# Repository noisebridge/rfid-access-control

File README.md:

RFID access control
-------------------

Access control system used within the [Noisebridge] hacker space.

   - RFID door terminal
      * [Firmware](software/firmware/README.md)
      * [PCB](hardware/terminal/README.md)
      * [3D printed case](hardware/terminal-case/README.md)
   - [Multi RS232 serial interface with RJ45](hardware/multi-interface/README.md)
   - [Earl: Central access control software](software/earl/README.md)

![RFID reader][case-image]

[case-image]: https://github.com/hzeller/rfid-access-control/raw/master/img/rfid-reader-case.png
[Noisebridge]: https://noisebridge.net/

## License

All code and PCB designs are released under the GNU General Public License V2, found in LICENSE

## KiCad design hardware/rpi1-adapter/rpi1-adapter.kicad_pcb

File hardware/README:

Case
   - a case to mount the RFID reader on the wall.

Boards
  - terminal board with RFID-RC522, providing a serial interface and potentially
    local switching
  - interface board on 'server' side, interfacing the Raspberry Pi or Beaglebone
    with the physical world of serial interfaces an relay switching.

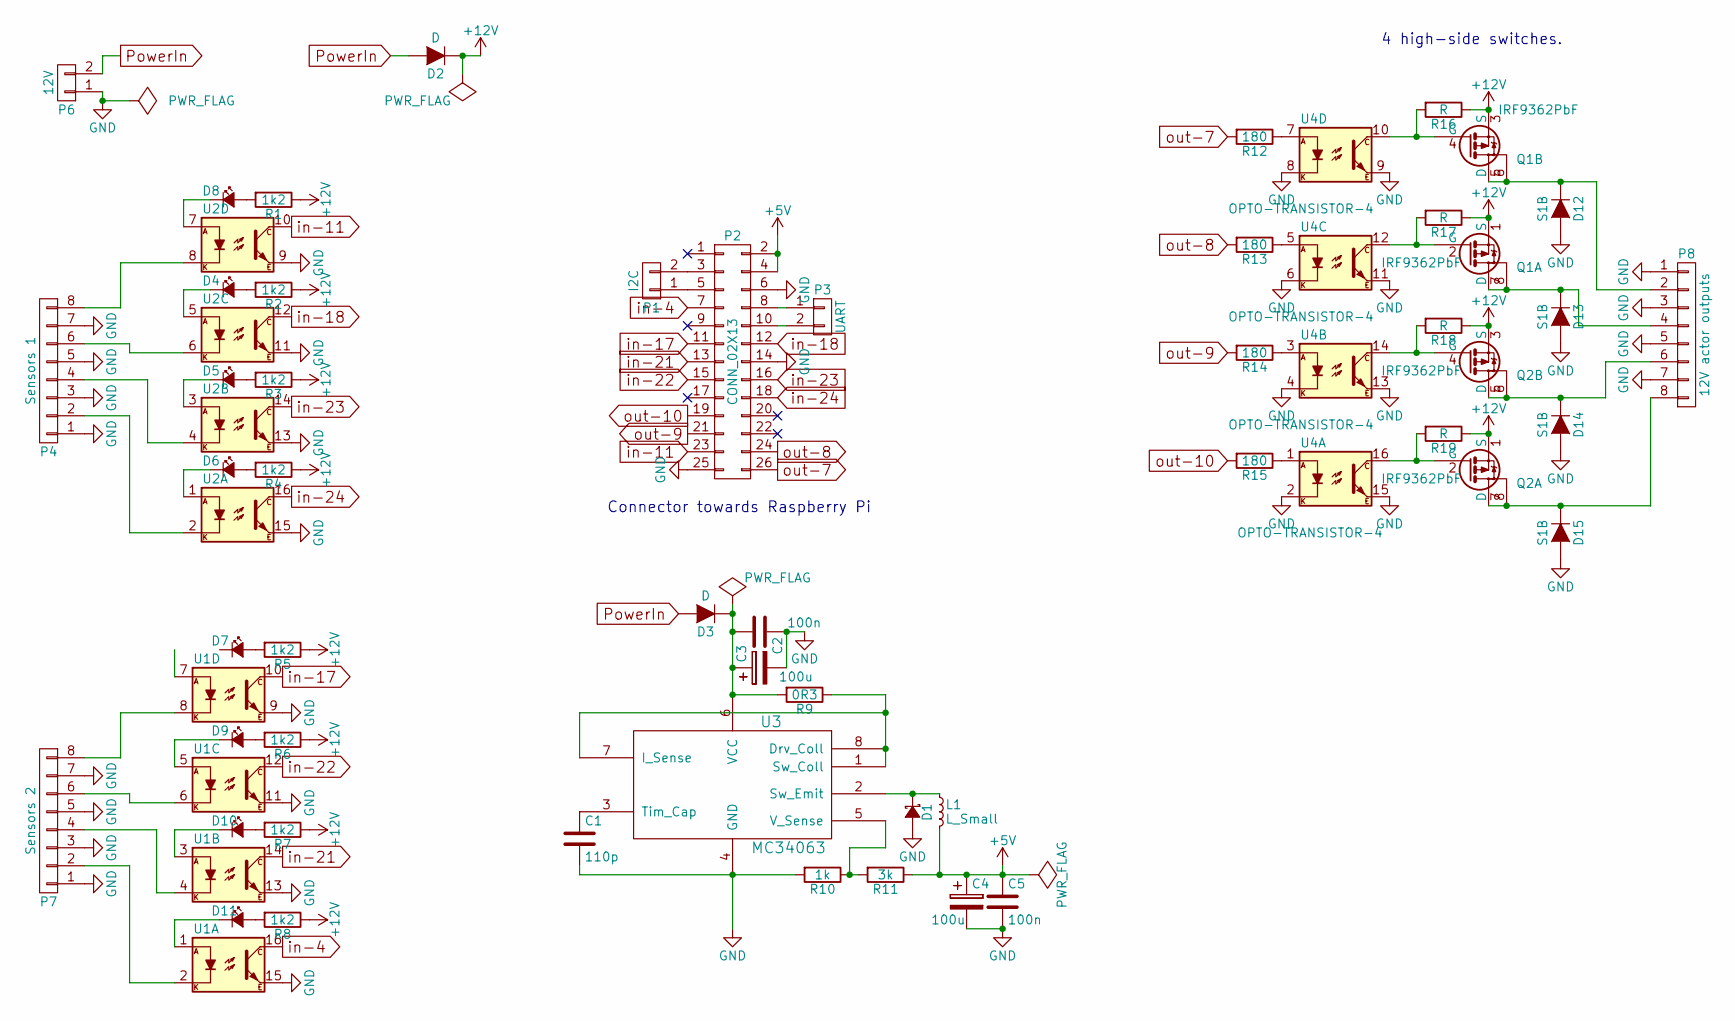
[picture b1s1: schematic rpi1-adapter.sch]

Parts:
C1: 110p; C_0805_HandSoldering
C2, C5: 100n; C_0805_HandSoldering
C3: 100u; C_Radial_D10_L16_P5
C4: 100u; C_1206_HandSoldering
D1: D_Schottky_Small; Diode-SMA_Handsoldering
D2, D3: D; Diode_DO-35_SOD27_Horizontal_RM10
D4, D5, D6, D7, D8, D9, D10, D11: Led_Small; LED-0805
D12, D13, D14, D15: S1B; Diode-SMA_Standard
L1: L_Small; INDUCTOR_V
P1: I2C; Pin_Header_Straight_1x02
P2: CONN_02X13; Pin_Header_Straight_2x13
P3: UART; Pin_Header_Straight_1x02
P4: Sensors 1; TerminalBlock-8pin-3.5mm
P6: 12V; JACK_ALIM
P7: Sensors 2; TerminalBlock-8pin-3.5mm
P8: 12V actor outputs; TerminalBlock-8pin-3.5mm
Q1, Q2: IRF9362PbF; SO-8
R1, R2, R3, R5, R6, R7, R8: 1k2; R_0805_HandSoldering
R4: 1k2; R_0805
R9: 0R3; R_0805_HandSoldering
R10: 1k; R_0805_HandSoldering
R11: 3k; R_0805_HandSoldering
R12, R13, R14, R15: 180; R_0805_HandSoldering
R16, R17, R18, R19: R; R_0805_HandSoldering
U1, U2, U4: OPTO-TRANSISTOR-4; DIP-16_W7.62mm_LongPads
U3: MC34063; SOIC-8_3.9x4.9mm_Pitch1.27mm

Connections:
+5V: C4.1, C5.1, L1.2, P2.2, P2.4, R11.1
+12V: D2.1 (K), Q1.1 (S), Q1.3 (S), Q2.1 (S), Q2.3 (S), R1.1, R2.1, R3.1, R4.1, R5.1, R6.1, R7.1, R8.1, R16.1, R17.1, R18.1, R19.1
GND: C1.2, C2.1, C3.2, C4.2, C5.2, D1.2 (A), D12.2 (A), D13.2 (A), D14.2 (A), D15.2 (A), P2.6, P2.14, P2.25, P4.1, P4.3, P4.5, P4.7, P6.1, P7.1, P7.3, P7.5, P7.7, P8.1, P8.3, P8.5, P8.7, R10.2, U1.9, U1.11, U1.13, U1.15, U2.9, U2.11, U2.13, U2.15, U3.4 (GND), U4.2, U4.4, U4.6, U4.8, U4.9, U4.11, U4.13, U4.15
unnamed: C1.1, U3.3 (Tim_Cap)
unnamed: C2.2, C3.1, D3.1 (K), R9.2, U3.6 (VCC)
unnamed: D1.1 (K), L1.1, U3.2 (Sw_Emit)
unnamed: D4.1 (K), U2.5
unnamed: D4.2 (A), R2.2
unnamed: D5.1 (K), U2.3
unnamed: D5.2 (A), R3.2
unnamed: D6.1 (K), U2.1
unnamed: D6.2 (A), R4.2
unnamed: D7.2 (A), R5.2
unnamed: D8.1 (K), U2.7
unnamed: D8.2 (A), R1.2
unnamed: D9.1 (K), U1.5
unnamed: D9.2 (A), R6.2
unnamed: D10.1 (K), U1.3
unnamed: D10.2 (A), R7.2
unnamed: D11.1 (K), U1.1
unnamed: D11.2 (A), R8.2
unnamed: D12.1 (K), P8.2, Q1.5 (D), Q1.6
unnamed: D13.1 (K), P8.4, Q1.7 (D), Q1.8
unnamed: D14.1 (K), P8.6, Q2.5 (D), Q2.6
unnamed: D15.1 (K), P8.8, Q2.7 (D), Q2.8
unnamed: P1.1, P2.5
unnamed: P1.2, P2.3
unnamed: P2.8, P3.1
unnamed: P2.10, P3.2
unnamed: P4.2, U2.2
unnamed: P4.4, U2.4
unnamed: P4.6, U2.6
unnamed: P4.8, U2.8
unnamed: P7.2, U1.2
unnamed: P7.4, U1.4
unnamed: P7.6, U1.6
unnamed: P7.8, U1.8
unnamed: Q1.2 (G), R17.2, U4.12
unnamed: Q1.4 (G), R16.2, U4.10
unnamed: Q2.2 (G), R19.2, U4.16
unnamed: Q2.4 (G), R18.2, U4.14
unnamed: R9.1, U3.1 (Sw_Coll), U3.7 (I_Sense), U3.8 (Drv_Coll)
unnamed: R10.1, R11.2, U3.5 (V_Sense)
unnamed: R12.1, U4.7
unnamed: R13.1, U4.5
unnamed: R14.1, U4.3
unnamed: R15.1, U4.1
PowerIn: D2.2 (A), D3.2 (A), P6.2
in-4: P2.7, U1.16
in-11: P2.23, U2.10
in-17: P2.11, U1.10
in-18: P2.12, U2.12
in-21: P2.13, U1.14
in-22: P2.15, U1.12
in-23: P2.16, U2.14
in-24: P2.18, U2.16
out-7: P2.26, R12.2
out-8: P2.24, R13.2
out-9: P2.21, R14.2
out-10: P2.19, R15.2

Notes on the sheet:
Connector towards Raspberry Pi
4 high-side switches.

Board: 2 copper layers, 53 parts (0 on the bottom side), 60 nets, no tracks yet.

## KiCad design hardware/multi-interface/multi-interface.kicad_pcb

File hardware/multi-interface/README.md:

Multi serial line driver RJ45
=============================

Features
--------
   - 4 interfaces with RJ45 plugs (uses a combined 4-block of RJ45 I found in
     an old switch. Standard distance would need to pull these apart 50 thou/mil)
   - TTL compatible with 3.3V, so can interface with Rasberry Pi or
     Beaglebone Black.
   - Creates RS232 line voltages from a single 3.3V supply.
   - Uses a [SP3232E][sp3232-spec], essentially a MAX232 compatible chip
     for 3.3V supply voltage and only 100nF capcitors needed.
   - Allows to power external terminals on Line 7 and 8 (see `../terminal` for
     details)
   - FYI M3 mounting holes are 18mmx64mm apart.

![PCB][pcb]

TODO
----
Learnings from first board, possibly add to second revision

   - It would be useful to have a four line voltage/ground connector, directly
      compatible with the corresponding 4-pin connector on the terminal side.
   - Silk-screen marking RX/TX
   - 3-Pin connector for 12v: [GND-12v-GND] to allow turn-agnostic plug.
   - Possibe protection circuit: reverse polarity protection diode; PTC fuse
   - optional 12V power LED ? Maybe optional 3.3V power LED
   - RX/TX LEDs. Check connection of RJ45 plugs, some have built-in LEDs
     (usually to indicate Ethernet 100Mbps/1Gbps), would be cool to re-use
     these. Also optional space for discrete diodes.
   - All LEDs: also provide pads on the bottom of the board if that is the
     part visible.
    
[pcb]: https://github.com/hzeller/rfid-access-control/raw/master/img/multi-interface-pcb.png
[sp3232-spec]: http://www.exar.com/common/content/document.ashx?id=619

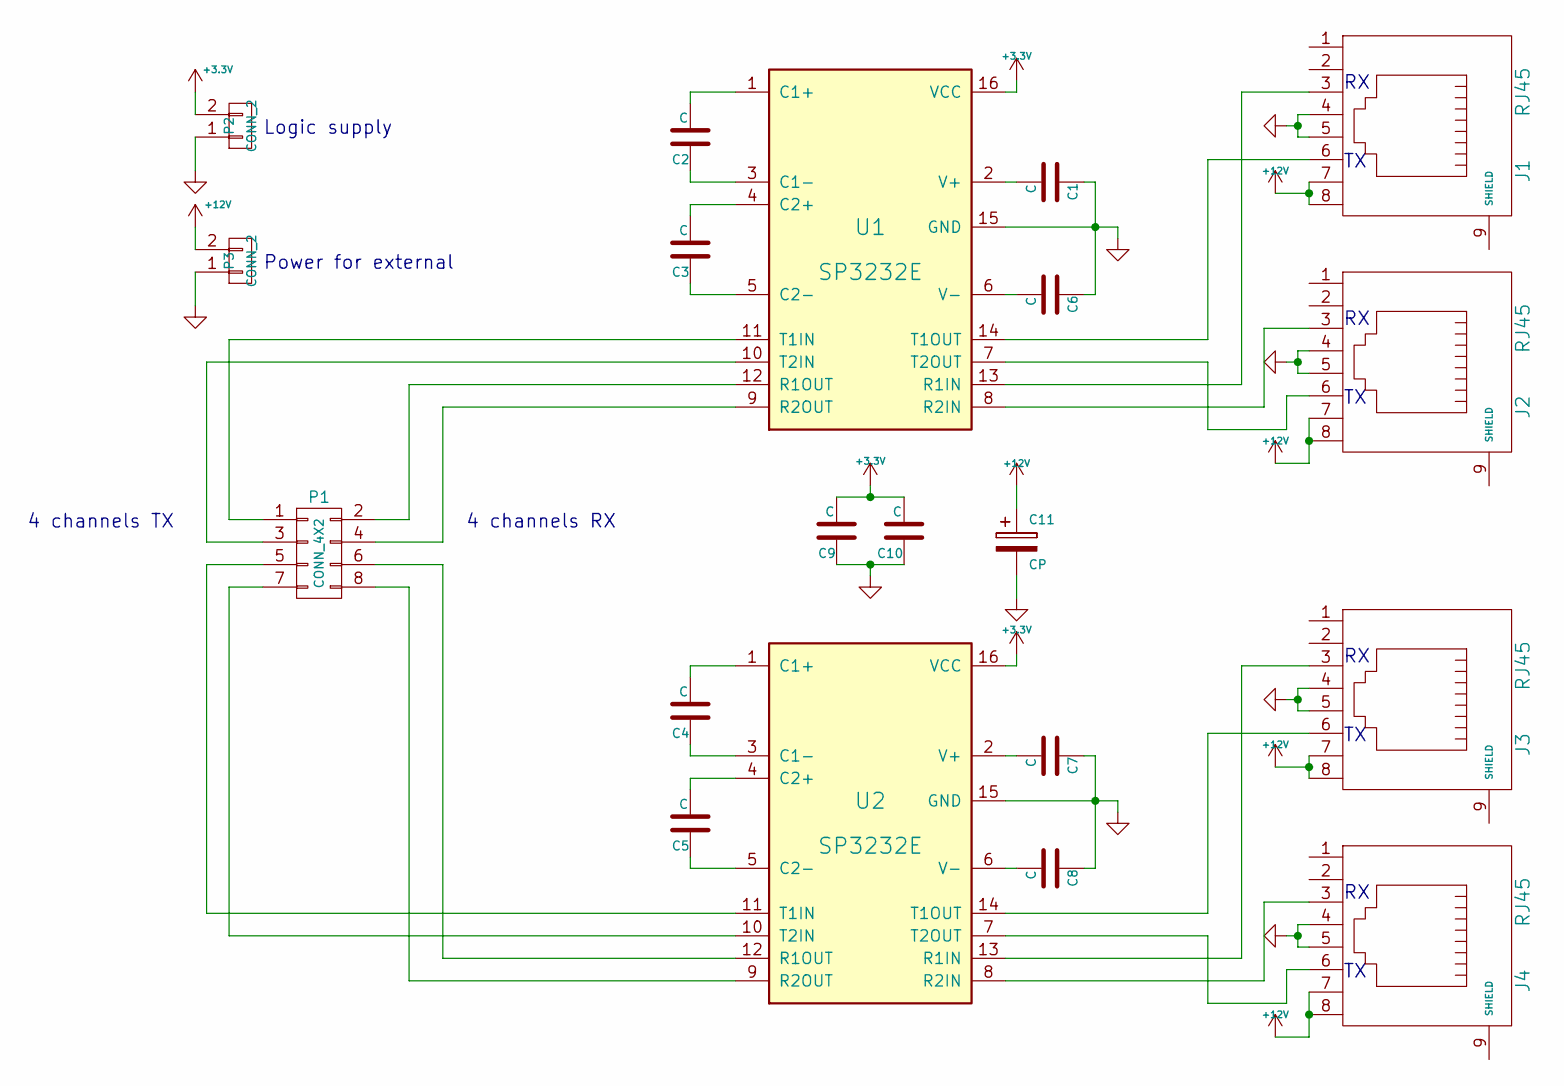
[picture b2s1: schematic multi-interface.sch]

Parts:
C1, C2, C3, C4, C5, C6, C7, C8, C9, C10: C; SMD-0805
C11: CP; Elko_vert_DM6-3_RM2-5
J1, J2, J3, J4: RJ45; RJ45_8
P1: CONN_4X2; Pin_Header_Straight_2x04
P2, P3: CONN_2; SIL-2
U1, U2: SP3232E; TSSOP-16

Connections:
+3V3: C9.2, C10.2, P2.2, U1.16 (VCC), U2.16 (VCC)
+12V: C11.1, J1.7, J1.8, J2.7, J2.8, J3.7, J3.8, J4.7, J4.8, P3.2
GND: C1.1, C6.1, C7.1, C8.1, C9.1, C10.1, C11.2, J1.4, J1.5, J2.4, J2.5, J3.4, J3.5, J4.4, J4.5, P2.1, P3.1, U1.15 (GND), U2.15 (GND)
unnamed: C1.2, U1.2 (V+)
unnamed: C2.1, U1.3 (C1-)
unnamed: C2.2, U1.1 (C1+)
unnamed: C3.1, U1.5 (C2-)
unnamed: C3.2, U1.4 (C2+)
unnamed: C4.1, U2.3 (C1-)
unnamed: C4.2, U2.1 (C1+)
unnamed: C5.1, U2.5 (C2-)
unnamed: C5.2, U2.4 (C2+)
unnamed: C6.2, U1.6 (V-)
unnamed: C7.2, U2.2 (V+)
unnamed: C8.2, U2.6 (V-)
unnamed: J1.3, U1.13 (R1IN)
unnamed: J1.6, U1.14 (T1OUT)
unnamed: J2.3, U1.8 (R2IN)
unnamed: J2.6, U1.7 (T2OUT)
unnamed: J3.3, U2.13 (R1IN)
unnamed: J3.6, U2.14 (T1OUT)
unnamed: J4.3, U2.8 (R2IN)
unnamed: J4.6, U2.7 (T2OUT)
unnamed: P1.1, U1.11 (T1IN)
unnamed: P1.2, U1.12 (R1OUT)
unnamed: P1.3, U1.10 (T2IN)
unnamed: P1.4, U1.9 (R2OUT)
unnamed: P1.5, U2.11 (T1IN)
unnamed: P1.6, U2.12 (R1OUT)
unnamed: P1.7, U2.10 (T2IN)
unnamed: P1.8, U2.9 (R2OUT)

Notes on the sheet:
4 channels RX
4 channels TX
Logic supply
Power for external

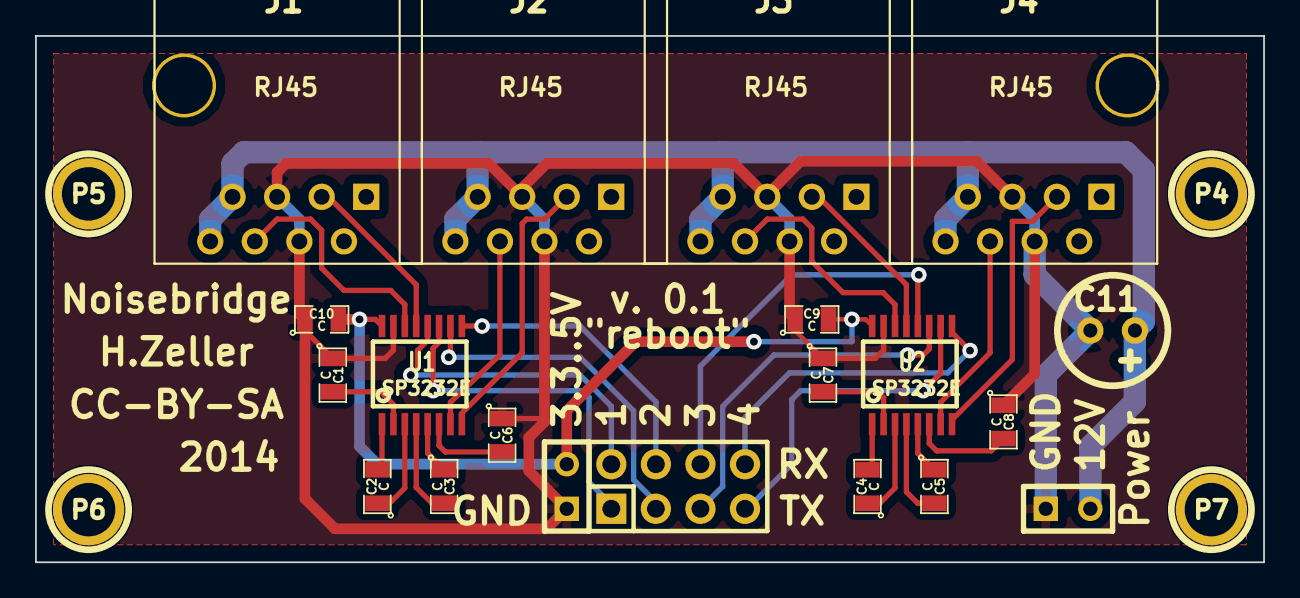
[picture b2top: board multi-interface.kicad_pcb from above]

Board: 2 copper layers, 70.0 x 30.0 mm, 24 parts (0 on the bottom side), 31 nets.

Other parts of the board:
P4, P5, P6, P7: CONN_1; 1pin

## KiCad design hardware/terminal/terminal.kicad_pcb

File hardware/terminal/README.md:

Terminal PCB
============

The Access terminal mounted at the outside of the door. Typically connecting the
RFID reader (via SPI interface), but also a 4x3 keypad (or just simple door-bell
button) and an LCD can be connected. If wanted, even an electric strike via
some external H-bridge.

This is based on an Atmega8 because I had a bunch lying around, but the DIL
version is bulky and ideally, I'd like to have a bit more IO pins, such as
for a 4th row of the keypad or separate LED outputs; future versions might
change to atmega168 (currently the best Atmel-IO bang for the buck).

This board provides the necessary breakouts to connect the peripherals to an
Atmega8 and holds the MAX232 compatible line driver.
The software in `../../software/firmware` makes it useful.

For a housing of this board and the RFID reader, have a look at
`../terminal-case`

Feature overview
----------------

   - Sized so that it can be sandwiched with a RFID-RC522 board (40mmx60mm),
     including the same mounting holes.
   - Communication via RS232, using standard RJ45 plug.
   - Separate 4-pin header to connect without RJ45
   - In-circuit programming header.
   - Uses Atmega8 in PDIP cases, mostly because I had a bunch lying around :)
   - Allows to connect RFID-RC522, 4x3 keypad, HD44780 LCD, RGB-LED,
     speaker-buzzer. All supported by firmware.
   - Uses a [SP3232E][sp3232-spec], essentially a MAX232 compatible chip
     for 3.3V supply voltage and only 100nF capcitors needed.
   - Uses the SP3232E charge pump to get the negative voltage needed to drive
     LCD contrast.
   - Little 'breadboard area' for quick hacks.

Serial connection with RJ45
---------------------------

Pinout of RJ45 is a somewhat 'standard' way to connect an RJ45 with RS232
and is used in [Various][rj45-terminal-1] [router][rj45-terminal-2]
terminal connections (But note to whoever came up with this first probably 20
years ago: **bad choice**! Pin 3 and 6 are twisted together in an ethernet
cable, so this just optimized crosstalk between RX and TX...).

We also power the terminal circuit via the RJ45. We use the fact that the
lines `DTR` and `RTS` can always be set to +12V safely (within RS232 voltage
range) from the host (=[Data Terminal Equipment; DTE][DTE]). We use that to
provide power to our terminal (for any other endpoint with RJ45, this set-up
would look like a benign 'always ready' flow control signal; so does not damage
equipment). With two lines providing power, it should be possible to power
smallish loads such as an electric strike even over a longer line without too
much voltage drop.

The following list is the RJ45 connections from view of the terminal,
the [DCE side][DCE].
The *Line* in the following list represents the corresponding RJ45 pin.
Also as reference gives the [9-pin Sub-D connector (DB9)][db9-pinout]
equivalent connection on a 'standard' connector.
NB: Depending on the wiring (T568A or T568B), the color of Line-3 is either
striped orange or green, the Line-6 solid orange or green.

   - Line 1: Not connected (usually: DCE:RTS (out) / DTE:CTS (in)) *DB9-8*
   - Line 2: Not connected (usually: DCE:DTR (out) / DTE:DSR (in)) *DB9-1*
   - Line 3: **TxD**  (on host DTE:RxD) *DB9-2* (orange or green striped)
   - Line 4: **GND** (on host DTE:RI, 'Ring indicator') *DB9-5* (DB9-9). (Blue solid).
   - Line 5: **GND** (GND) *DB9-5* (Blue striped).
   - Line 6: **RxD** (on host DTE:TxD) *DB9-3*  (orange or green solid)
   - Line 7: **12V** supply in (usually: DCE:DSR (in) / DTE:DTR (out), DB9-4; but not connected there, just constantly powered. (Brown striped).
   - Line 8: **12V** supply in (usually: DCE:CTS (in) / DTE:RTS (out), DB9-7; powered, dito) (Brown solid).

(Let's see how well RS232 works, if long lines create trouble, we might consider
RS422 physical).

Hacking DB9 to RJ45 connector
------------------------------
If you want to have a standard DB9-female to RJ45 connector work with
this terminal, you need to hack it: open it up, and *disconnect* the cables
that go to **DB4** and **DB7** and instead connect them to an external 12V
power supply, with ground connected to **DB5** (ideally, you'd provide some
current limiting like 500mA to the 12V line; so if things go wrong, not
catastrophically so).

Double check on the RJ45 connector, that line 4 and 5 are on ground,
Line 7 and 8 on +12V.

![PCB][pcb]

Assembly
--------
Watch out in this version of the board, the [LD1117] LDO has to be soldered
in differently than the board suggests.

Unfortunately, it has a different pintout than other voltage regulators, this
is why it slipped in. Instead of [`Vin`, `GND`, `Vout`], it is
[`GND`, `Vout`, `Vin`]. So you need to solder in some lead-twisting :)

Tip for the RC522 reader. Depending on how you sandwich it, the chrystal oscillator it
has on top pokes out to the front; it might make sense to resolder it and put on the back
of the board.

TODO
----
TODOs for future versions; learning from previous board

   - Switch to atmega168 with less bulky 32 TQFP and 4 more IO pins.
   - Fix pin-out of LDO (also, switch to ceramic capacitors for less
     board height)
   - In general optimize board for best stacking, e.g. avoid collision with
     the crystal on the RFID board.
   - Provide an extra fourth column for keypad.
   - separate connector for 4st row, 4th column for an optional door-bell.
   - Silkscreen label all the pins for RC522 to minimize confusion which way
     to stack.
   - separate out RGB LEDs from LCD (when more IO available)
   - Maybe provide a reverse 8x2 connector for LCD (some LCDs are better
     connected from the reverse side)
   - Provide additional 16x1 connector to simply connect these LCD types.
   - Directly mount RGB LED on bord for less mouting hassle
   - Separate RX/TX connector on TTL side for easier testing.
   - Add space for 754410 to possibly directly drive door-strikes.
   - Add space for extra transistor to amplify speaker output.
   - Add space for little buzzer on-board.
   - Input for a reed switch to detect open doors ?

![Schematic][schematic]

[pcb]: ../../img/terminal-pcb.png
[schematic]: ../../img/terminal-sch.png
[sp3232-spec]: http://www.exar.com/common/content/document.ashx?id=619
[rj45-terminal-1]: http://www.allpinouts.org/index.php/Cisco_Console_RJ45_to_DB9_Pin
[rj45-terminal-2]: http://kb.juniper.net/InfoCenter/index?page=content&id=KB13272
[db9-pinout]: http://www.db9-pinout.com/
[DTE]: http://en.wikipedia.org/wiki/Data_terminal_equipment
[DCE]: http://en.wikipedia.org/wiki/Data_circuit-terminating_equipment
[LD1117]: http://www.st.com/web/en/resource/technical/document/datasheet/CD00000544.pdf

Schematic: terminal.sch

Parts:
C1, C2, C3, C4, C5, C6, C9: C; c_0805
C7, C8: CP; Elko_vert_DM5_RM2-5
IC1: ATMEGA8-P; DIP-28__300
J1: RJ45; RJ45_8
P1: Prog; SIL-5
P2: RC522; SIL-8
P3: LCD; Pin_Header_Straight_2x08
P4: Keypad; Pin_Header_Straight_2x08
P5, P6, P7, P8: CONN_1; 1pin
P9: CONN_2X2; Pin_Header_Straight_2x02
P10, P12: CONN_4; SIL-4
P11, P14: CONN_5X2; Pin_Header_Straight_2x05
P13: CONN_3X2; Pin_Header_Straight_2x03
R1, R5: 2.2k; SMD-0805
R2: 2.2k; SM0805
R3, R4: 82; SM0805
R6: 3k; SMD-0805
R7: 12; SMD-0805
U2: SP3232E; TSSOP-16
U3: 7803; LM78XXV

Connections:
+3V3: C5.1, C6.1, C8.1, C9.1, IC1.7 (VCC), P2.8, P3.2, R1.1, R2.1, R7.1, U2.10 (T2IN), U2.16 (VCC), U3.VO
+12V: C7.1, J1.7, J1.8, P10.4, U3.VI
/CS-RFID: IC1.16 ((~SS~/OC1B)PB2), P2.1, R1.2
/RST-RFID: IC1.15 ((OC1A)PB1), P2.7
GND: C3.1, C4.1, C5.2, C6.2, C7.2, C8.2, C9.2, IC1.8 (GND), J1.4, J1.5, J1.9 (SHIELD), P1.1, P2.6, P3.1, P3.5, P3.16, P4.2, P4.4, P4.6, P4.8, P4.10, P4.12, P4.14, P4.16, P9.1, P9.3, P10.1, R5.2, U2.8 (R2IN), U2.15 (GND), U3.GND
KCOL-0: IC1.14 ((ICP)PB0), P4.7
KCOL-1: IC1.9 (PB6(XTAL1/TOSC1)), P4.5
KCOL-2: IC1.10 (PB7(XTAL2/TOSC2)), P4.3
KROW-0: IC1.6 ((XCK/T0)PD4), P4.15
KROW-1: IC1.11 ((T1)PD5), P4.13
KROW-2: IC1.12 ((AIN0)PD6), P4.11
KROW-3: IC1.13 ((AIN1)PD7), P4.9
LCD-D0: IC1.23 ((ADC0)PC0), P3.11
LCD-D1: IC1.24 ((ADC1)PC1), P3.12
LCD-D2: IC1.25 ((ADC2)PC2), P3.13
LCD-D3: IC1.26 ((ADC3)PC3), P3.14
LCD-EN: IC1.28 ((ADC5/SCL)PC5), P3.6
LCD-RS: IC1.27 ((ADC4/SDA)PC4), P3.4
LCD-contr: R6.2, U2.7 (T2OUT)
MISO: IC1.18 ((MISO)PB4), P1.3, P2.4
MOSI: IC1.17 ((MOSI/OC2)PB3), P1.4, P2.3
unnamed: C1.1, U2.1 (C1+)
unnamed: C1.2, U2.3 (C1-)
unnamed: C2.1, U2.4 (C2+)
unnamed: C2.2, U2.5 (C2-)
unnamed: C3.2, U2.2 (V+)
unnamed: C4.2, U2.6 (V-)
unnamed: IC1.1 (PC6(~RESET~)), P1.5, R2.2
unnamed: IC1.4 ((INT0)PD2), R3.2
unnamed: IC1.5 ((INT1)PD3), R4.2
unnamed: P3.3, R5.1, R6.1
unnamed: P3.15, R7.2
unnamed: P9.2, R3.1
unnamed: P9.4, R4.1
RX: IC1.2 ((RXD)PD0), U2.12 (R1OUT)
RX-ext: J1.6, P10.3, U2.13 (R1IN)
SCK: IC1.19 ((SCK)PB5), P1.2, P2.2
TX: IC1.3 ((TXD)PD1), U2.11 (T1IN)
TX-ext: J1.3, P10.2, U2.14 (T1OUT)

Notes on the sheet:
Playground Area
Background Light

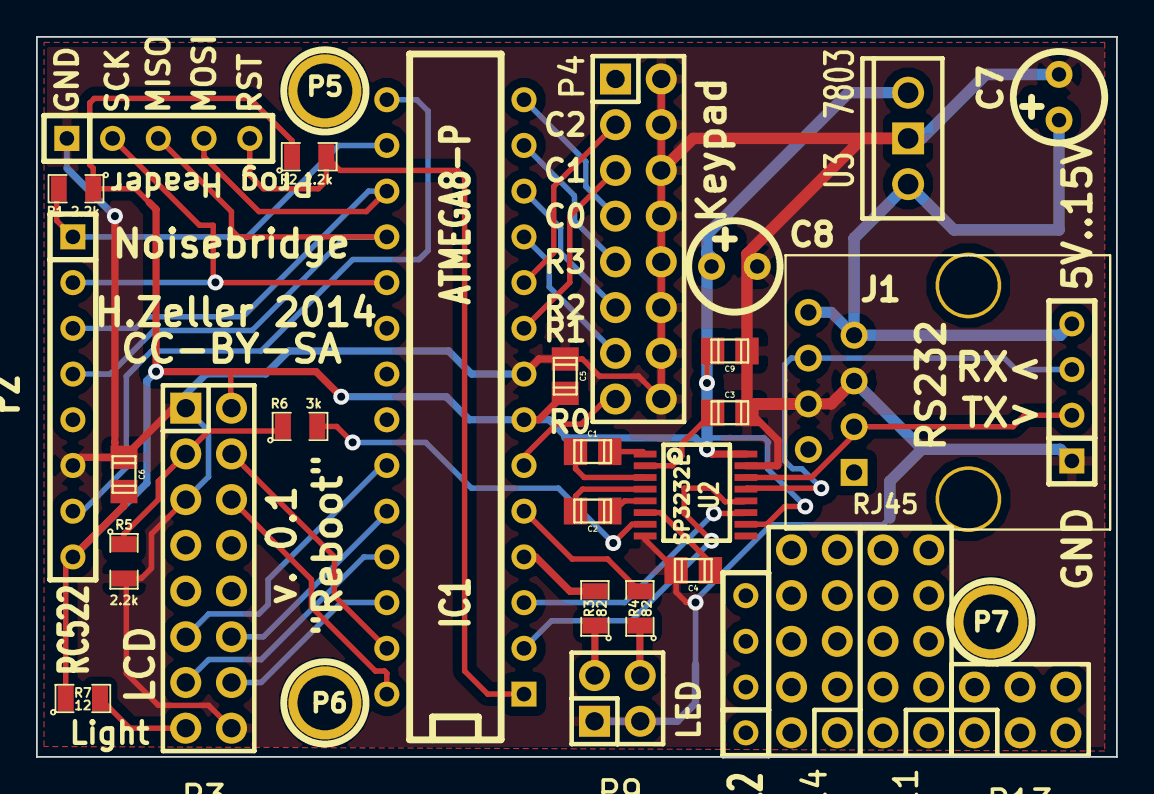
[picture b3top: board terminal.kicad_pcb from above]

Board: 2 copper layers, 60.0 x 40.0 mm, 33 parts (0 on the bottom side), 39 nets.

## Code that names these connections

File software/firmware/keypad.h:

/* -*- mode: c++; c-basic-offset: 2; indent-tabs-mode: nil; -*-
 * Copyright (c) h.zeller@acm.org. GNU public License.
 */

#ifndef AVR_KEYPAD_H_
#define AVR_KEYPAD_H_

#include "clock.h"

// For wiring more like 'pretty' physical layout, logical layout is a mess
// with bits distributed between ports :)
// row 1:PD7 2:PD6 3:PD5 4:PD4  (all port D; conveniently shifted by 4)
// col 1:PB0 2:PB7 3:PB6        (all port B)
class KeyPad {
  enum {
    // We read from Port-D to top 4 bits
    ROW_PORTD_SHIFT = 4,

    // Columns will be outputs on Port-B
    COL_1 = (1<<0),
    COL_2 = (1<<6),
    COL_3 = (1<<7),
    PORTB_OUT_MASK = COL_1 | COL_2 | COL_3,
  };

public:
  KeyPad();

  // This method needs to be called regularly.
  // It returns the current character pressed on the keypad if it settled
  // for long enough (it returns it only once, no auto-repeat).
  // Returns a NUL character ('\0') if no key is pressed.
  char ReadKeypad();

private:
  typedef unsigned char keypad_state_t;
  keypad_state_t SampleCol(unsigned char col_sample_bit,
                           keypad_state_t col_data);
  keypad_state_t readKeypadState();

  keypad_state_t current_state_;
  bool character_returned_;
  Clock::cycle_t start_time_;
};

#endif  // AVR_KEYPAD_H_

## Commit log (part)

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2014-08-28 o Move third party mfrc library in separate directory
2014-08-28 o rename ALLOW_BAUD_CHANGE -> FEATURE_BAUD_CHANGE
2014-09-01 o Some pseudo-code. To be removed, code should be go
2014-09-03 o sandwich turned out a bit thicker.
2014-09-03 o Update README with specs.
2014-09-03 o qualify Baron with a link.
2014-09-03 o Update readme.
2014-09-03 o Rename host -> earl. As this is our go package name.
2014-09-03 o fix typo.
2014-09-03 Initial submit of earl server with a debug handler.
2014-09-03 o Update build doc.
2014-09-03 o add GetTerminalName()
2014-09-03 o add comment regarding implementation of timeout.
2014-09-03 o more fmt -> log conversions.
2014-09-14 First draft of SSH server
2014-09-26 More authenticator work
2014-10-20 o Make keypress timeout dependent on time not ticks
2014-10-23 o Add assembly caveat.
2014-10-25 o Provide a flag toggle command to set operational flags. o Use that to switch on/off keypad tone feedback.
2014-10-25 Clean up code handling a bit
2014-10-26 It works!
2014-10-26 o Make TerminalStub an interface. That way, we can write unittests.
2014-10-26 o Little comment updates. o Do tick every 500ms
2014-10-27 o Do name dispatching.
2014-10-27 Use time.Duration for durations.
2014-10-27 o Move actions (operate relays) into GPIOActions and make DoorActions an interface.
2014-10-27 o A bit nicer timeout handling.
2014-10-27 Test for AccessHandler.
2014-10-28 o Add AddNewUser() in authenticator o Basic test for authenticator
2014-10-28 o Refine test a bit
2014-10-28 o Make user files configurable with flags.
2014-10-28 o Simplify switch/case that only contains one case with if
2014-10-28 o Be more in the spirit of Go and use ugly constant names (Did the commit message sound judging in any way ?)
2014-10-29 o stub for a time-test.
2014-10-29 o Move user-level to the front.
2014-10-29 o Just learned about the comma-separation of cases in switch.
2014-10-29 o Log if a door is opened.
2014-10-29 o Install: use install instead of cp, otherwise 'busy textfile' o time: make 22 inclusive
2014-10-29 o Remove a former todo.
2014-10-30 o We still want to find users with too short code; just not authenticate.
2014-10-30 o Update comments.
2014-10-31 o Add concept of expiry of codes without a contact info. Without contact info, it is not possible to find the 'right' line to remove in CSV in case the token is lost or stolen - people usually don't 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
2014-10-31 o Accidentally created validUsers map twice.
2014-10-31 o Instead of just logging error conditions, bubble them up using Go's tuple return. That way, they can be used/presented where needed.
2014-10-31 o Simple base-plates to mount inside box.
2014-11-02 o Add baseplate design files.
2014-11-03 o Logging: add starting info.
2014-11-03 o fix typo
2014-11-03 o A bit more logging how many codes were read.
2014-11-03 o Rename Handler to TerminalEventHandler : better reflects what it is doing.
2014-11-05 o Both plates are the same width, so make the holder for it a bit wider. Let's see if the overhang is managed properly by the printer.
2014-11-05 o Remove legacy file support. If we want to add PIN code access we still can do that with the new file format, no need to keep the old one.
2014-11-05 o DoorAction: Make logging more consistent for grepping.
2014-11-05 o More detailed stats while loading file.
2014-11-05 o Reasons for non-auth: handle most specific first.
2014-11-07 o initial version control terminal
2014-11-08 o Test validity of Level while reading.
2014-11-10 o make side-holder with step.
2014-11-10 o Remove feature to directly write to outputs. Was needed in debugging but not anymore.
2014-11-12 o if the manual drilled holes don't fit the print, make the print fit the holes ...
2014-11-12 o A bit more qualified messages on UI display.
2014-11-13 o Add an compile-optional feature to query the MFRC522 registers for debugging purposes.
2014-11-14 o remove obsolete comment.
2014-11-30 o Power colors.
2015-01-20 o Simplify earl startup.
2015-01-20 o ... make compile
2015-01-21 o Start a more random number for user-id generation.
2015-01-21 o Old compilers can't see unreachable code.
2015-01-22 o Make it possible to compile-in terminal name. o directly read from EEPROM when querying name; no need to copy it to RAM first.
2015-01-25 o Remove yeoman for now.
2015-01-25 o Move case/ -> terminal-case/
2015-01-26 o initial stub for UpdateUser() (TODO: persist)
2015-01-26 o readme.
2015-01-27 o progress database
2015-01-28 o Enable brown-out fuse (yeah, was disabled all the time :/) o Skip first byte in EEPROM, as this seems to be most vulnerable in power-glitch situations.
2015-01-28 o Provide update user.
2015-01-28 o Simple update user.
2015-01-28 o Rename TerminalStub to TerminalImpl o Re-arrange some methods for readability (public methods first, then private) in TerminalImpl. o make all private methods lower-case o IdleTick: It can starve, 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
2015-01-28 o Add doorbell action - if user out of daytime attempts to open door (and gets 'blue' result), it automatically triggers the doorbell. - Pressing a single '#' on the keypad without any number trigger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
2015-01-29 o Don't explicitly log door open events (SD card wear!)
2015-01-30 o Make it possible to query the access hours.
2015-01-30 o Use access hour query to display in UI
2015-01-31 o (untested): first bell UI
2015-01-31 o Better alignment of LCD text.
2015-01-31 o smallish tweaking.
2015-01-31 o Ugh, need to run as root :/
2015-01-31 o Random small text changes.
2015-02-03 o Make state machine robust in case of corrupted bits. Interestingly, this uses 14Bytes _less_ program code.
2015-02-04 o Some smallish doc updates.
2015-02-04 o Move terminal interface into separate file.
2015-02-08 o Make doorbell work by just aplay-ing
2015-02-08 o make work with older compilers.
2015-02-08 o revert Makefile to before.
2015-02-08 o Allow [5] to open door for now as well.
2015-02-12 o Switch to the concept of using an ApplicationBus. This simplifies cross-thread communication and will it make very easy to have out-of-band triggering or reporting (e.g. with some JSON webserver).
2015-02-12 o Rate limit door-strike opening relay (in particular: don't interfere with ourselve just opening).
2015-02-12 o Add timestamp to each event.
2015-02-13 o fix some displaying mode. o use ?callback instead of ?jsonp for callbak name passing.
2015-02-14 o Make messages a bit more useful.
2015-02-14 o little LCD optimized messages.
2015-02-14 o Make law-abiding browsers relax.
2015-02-17 o Emit user management events on bus.
2015-02-19 o Show the last events that happened.
2015-02-20 o Add IsHistoricEvent tag for events emitted prior to API connect. o Provide a 'earl started' event which could be useful.
2015-02-22 o ... forgot event.
2015-02-28 o Provide a flag to just list users then exit.
2015-03-04 Add optional -version flag.
    Makefile's earl command now sets the VERSION symbol to a nice string w/
    git SHA of HEAD and the date.
2015-03-04 Remove whitespace from VERSION string
    the ARM linker doesn't like it :(
2015-03-07 o Emit version number in starting event.
2015-04-09 typo
2015-04-29 import astrotime from cpucycle rather than copying library into this repository
2015-05-03 Update user.go
    Added the package astrotime + geographical coordinates of Noisebridge
    Opening at sunrise for fullTimeUser
    Opening at sunrise + 3 for user
2015-05-03 Update authenticator.go
    open at sunrise + amend mockclock in tests to be date aware
2015-05-06 fixed longitude
2015-05-14 o Make test work with this.
2015-06-06 o remove unneeded library.
2015-06-07 o correct some paths to find the 3D components.
2015-06-07 o properly turn the 3D model of TSSOP 16 o Update rendered image
2015-06-16 o Make screw terminal solder pads more beefy.
2015-06-20 o work in progress..
2015-06-25 o Add default housing to dual p-channel transistor.
2015-06-26 o Get rid of duplicate component name in description.
2015-09-02 o Allow to press hush button multiple times for hushing. o Opening a door will unhush.
2015-09-02 o Use right variable to calculate current hush time.
2015-09-27 Added longer duration for showing the doorbell on display.
2015-12-24 o philanthropist is a long word .. adapt printf() formatting o when loading the csv file: show how many expired users we have.
2016-02-26 o Printable STLs
2016-03-02 Bump the doorbell timeout to 30 secons
2016-08-09 o De-flake opening test. We need to wait for the open event first before checking for green color LED.
2016-12-20 Bump hiatus start date to 21st UTC
2016-12-28 o Add schematic.
2016-12-28 o Make timer work.
2016-12-28 o back to mega8
2017-02-19 Add LICENSE file and section in README.md
2017-08-26 Type of event changed from int to string.
2017-08-26 More testing for authenticator roles.
2017-08-26 o Centralize allowed operations per level.
2017-08-26 Output user name when renewal needed.
2018-03-07 Even more time
2018-03-24 <3 tests!
2018-06-22 Increase show doorbell duration from 75 to 120 seconds
2018-10-25 Allow Philanthropists to also add new users. (Result from meeting 2018-10-23 https://www.noisebridge.net/wiki/Meeting_Notes_2018_10_23 )
2018-11-15 Adds control panel feature upgrades (#30)
    * Allow doorbell-less rfid opens
    * Increase show doorbell duration from 75 to 120 seconds.
2018-11-15 Add @rizend's implementation of Philanthropist 30 day granting.
2018-11-15 No network stall on pegasus doorbell (#33)
    * Make doorbell ring request to pegasus timeout gracefully not hang.
    With recent network issues, we encountered that Earl run into trouble.
    Possibly because it couldn't reach pegasus and was patiently waiting
    for doorbell requests to come back, while exhausting local threads.
2018-12-29 Add CircleCI build
    Automatically build x86 and arm binaries.
2018-12-29 Add CircleCI build (#36)
    * Add CircleCI build (Automatically build x86 and arm binaries.)
    * Fix version build
2018-12-30 Fix typo in VERSION. (#37)
    .. to have git version hash properly included in binary.
2018-12-30 Disable pegasus doorbell due to network delays which makes it not line up with directly connected doorbell.
2018-12-30 Add Prometheus metrics.
    * Add Prometheus metrics handler.
    * Add build info metric.
    * Update Makefile to add version metric info.
2018-12-31 Add more Prometheus metrics.
2018-12-31 Update format.
2019-01-04 Fixup Auth counter
    * Use Consts for AuthResult string conversion.
    * Iterate over all Targets and AuthResults to init counters.
2019-01-04 Unexport Targets and AuthResults.
2019-01-04 Fix style.
2019-01-04 Register Prometheus metrics (#44)
    * Register auth and http metrics.
    * Init "GET" and "POST" http methods.
2019-01-04 Adjust AuthUser() returns (#45)
    * Set return variables to correctly pass data to defer.
    * Fix AuthUser() metric name.
2019-01-05 Fix auth results metric name.
2019-01-05 Fix http API metric observation
    Wrap defer in anonymous func to avoid evaluating time.Since() early.
2019-01-05 Add a deploy script to deploy earl from tagged github version.
2019-03-06 Use make -C.
2019-09-23 Update build
    * Simplify executor selection.
    * Bump to Go 1.13.
2020-08-01 Fix CircleCI
    Add missing checkout.
2020-08-04 Ignore bin dir for release pipeline (#53)
    Avoid dirty git state when publishing.

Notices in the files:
hardware/multi-interface/multi-interface.kicad_pcb:
CC-BY-SA
